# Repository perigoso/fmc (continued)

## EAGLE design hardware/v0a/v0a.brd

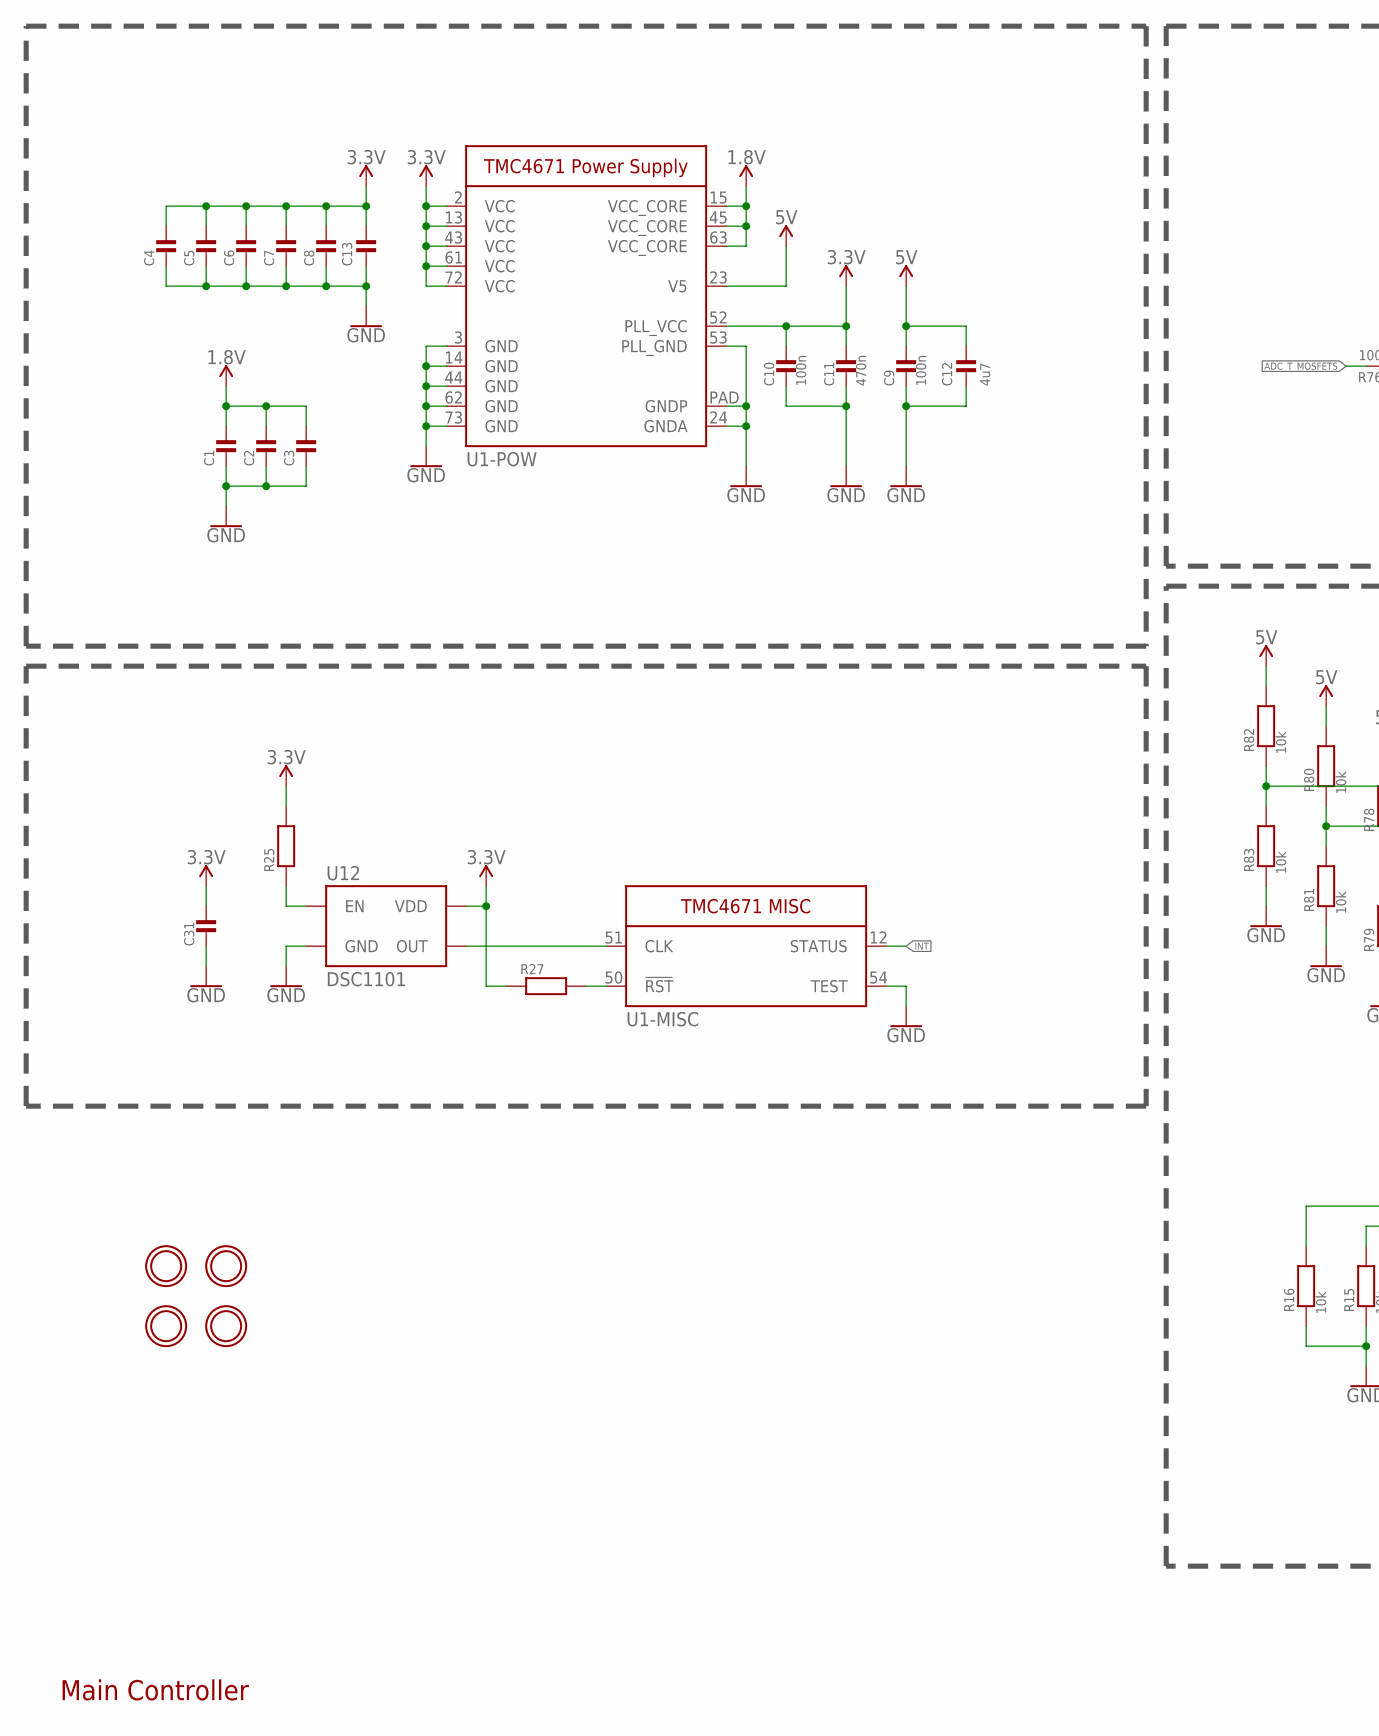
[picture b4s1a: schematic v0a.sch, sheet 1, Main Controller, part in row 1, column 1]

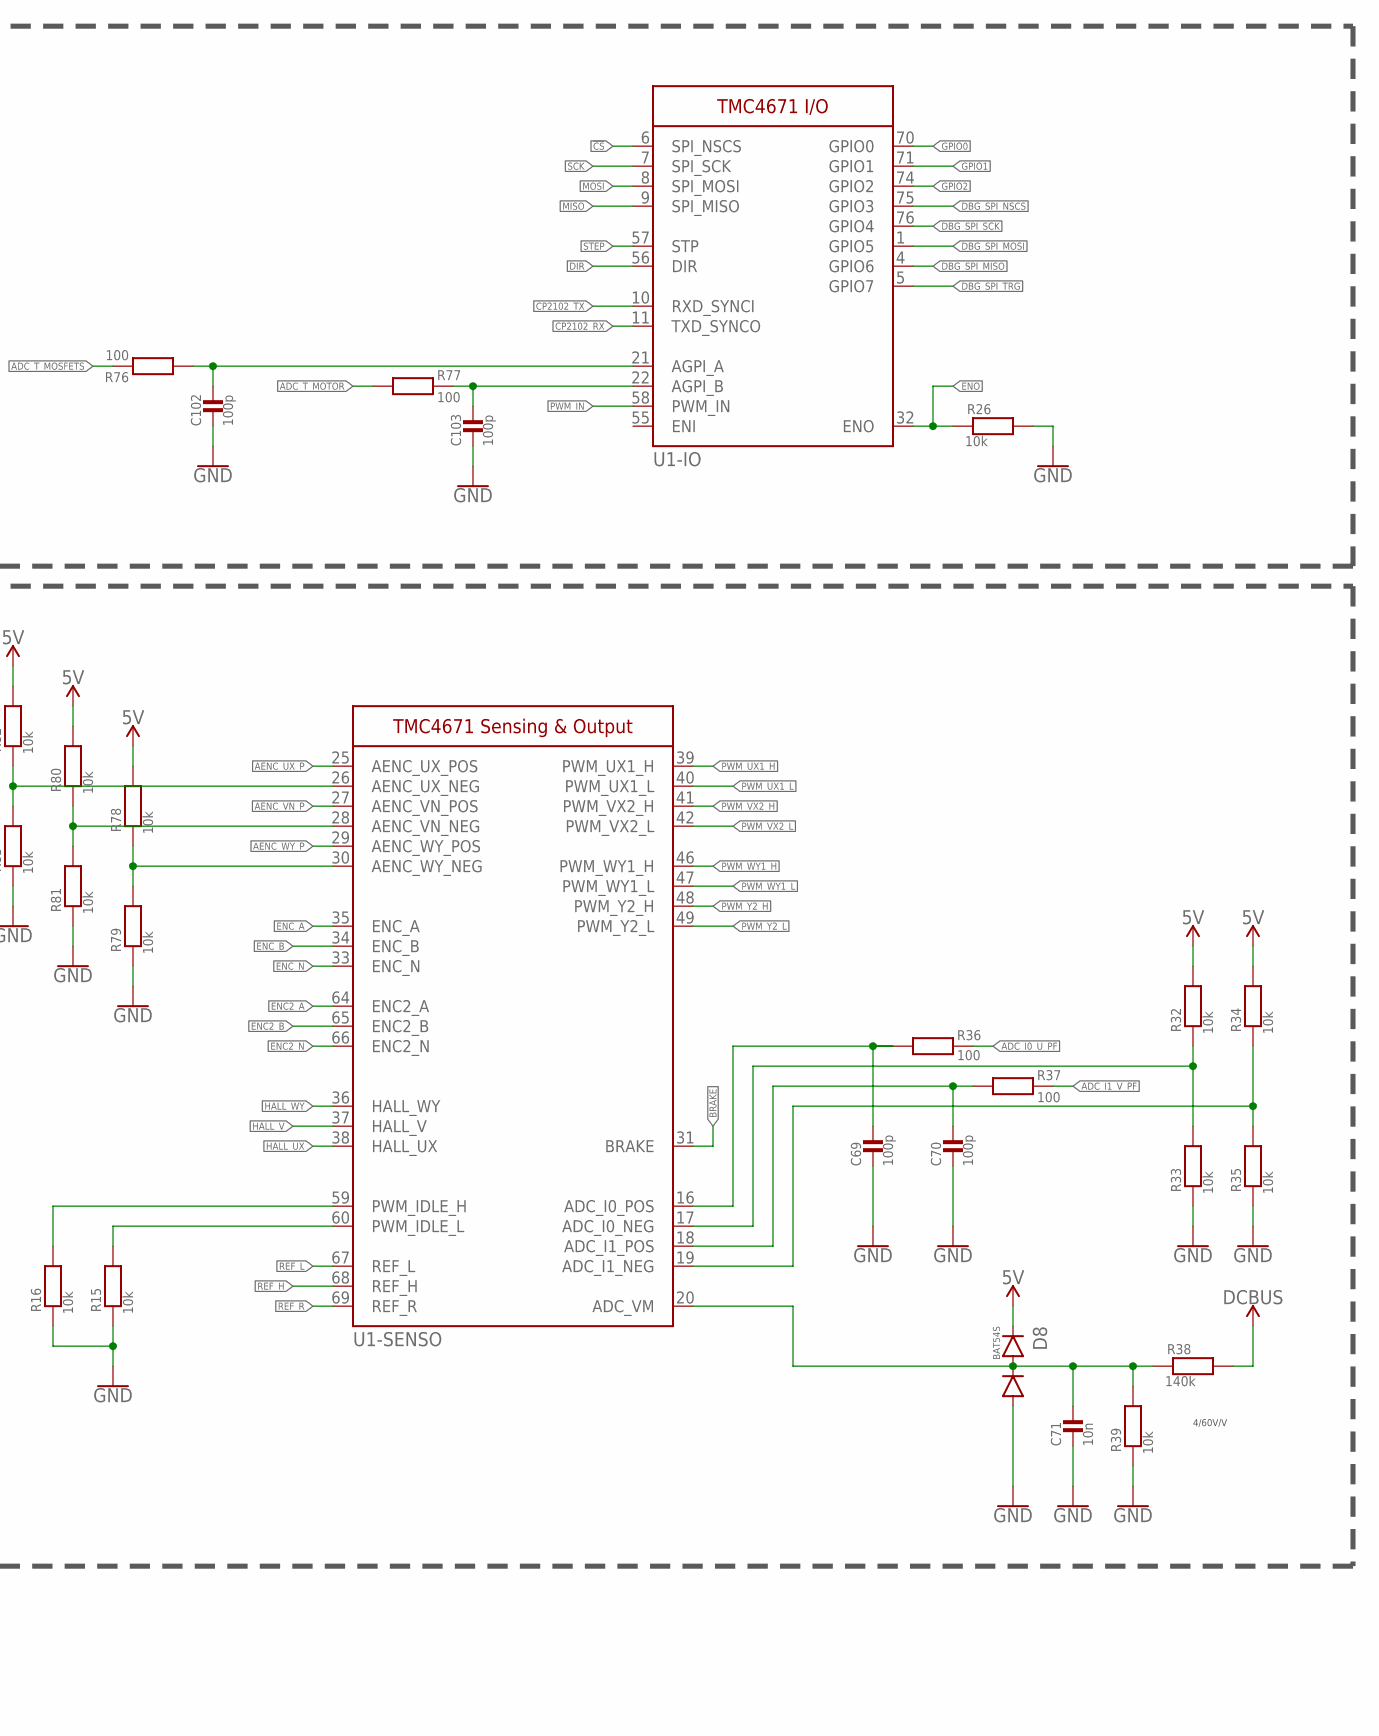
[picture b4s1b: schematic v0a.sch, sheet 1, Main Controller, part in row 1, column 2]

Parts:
C1, C2, C3, C4, C5, C6, C7, C8, C13, C31: MLCC0603; 0603_WAVE
C9, C10: 100n; 0603_WAVE
C11: 470n; 0603_WAVE
C12: 4u7; 0603_WAVE
C69, C70, C102, C103: 100p; 0603_WAVE
C71: 10n; 0603_WAVE
D8: BAT54S; SOT-23-3
R15, R16, R26, R32, R33, R34, R35, R39, R78, R79, R80, R81, R82, R83: 10k; 0603_WAVE
R25, R27: RESISTOR0603; 0603_WAVE
R36, R37, R76, R77: 100; 0603_WAVE
R38: 140k; 0603_WAVE
U1: TMC4671; QFN76
U12: DSC1101; CDFN_5X3.2
U$12, U$13, U$15, U$16: MOUNTINGHOLE3.0; MOUNTINGHOLE_3.0_PLATED

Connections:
1.8V: C1.P$1, C2.P$1, C3.P$1, U1.15 (VCC_CORE), U1.45 (VCC_CORE), U1.63 (VCC_CORE)
3.3V: C4.P$1, C5.P$1, C6.P$1, C7.P$1, C8.P$1, C10.P$1, C11.P$1, C13.P$1, C31.P$1, R25.P$2, R27.P$1, U1.2 (VCC), U1.13 (VCC), U1.43 (VCC), U1.52 (PLL_VCC), U1.61 (VCC), U1.72 (VCC), U12.6 (VDD); also elsewhere on the board
5V: C9.P$1, C12.P$1, D8.P$2 (2), R32.P$2, R34.P$2, R78.P$2, R80.P$2, R82.P$2, U1.23 (V5); also elsewhere on the board
!CS: U1.6 (SPI_NSCS); also elsewhere on the board
ADC_I0_U_PF: R36.P$2; also elsewhere on the board
ADC_I1_V_PF: R37.P$2; also elsewhere on the board
ADC_T_MOSFETS: R76.P$2; also elsewhere on the board
ADC_T_MOTOR: R77.P$1; also elsewhere on the board
AENC_UX_P: U1.25 (AENC_UX_POS); also elsewhere on the board
AENC_VN_P: U1.27 (AENC_VN_POS); also elsewhere on the board
AENC_WY_P: U1.29 (AENC_WY_POS); also elsewhere on the board
BRAKE: U1.31 (BRAKE); also elsewhere on the board
CP2102_RX: U1.11 (TXD_SYNCO); also elsewhere on the board
CP2102_TX: U1.10 (RXD_SYNCI); also elsewhere on the board
DBG_SPI_MISO: U1.4 (GPIO6); also elsewhere on the board
DBG_SPI_MOSI: U1.1 (GPIO5); also elsewhere on the board
DBG_SPI_NSCS: U1.75 (GPIO3); also elsewhere on the board
DBG_SPI_SCK: U1.76 (GPIO4); also elsewhere on the board
DBG_SPI_TRG: U1.5 (GPIO7); also elsewhere on the board
DCBUS: R38.P$2; also elsewhere on the board
DIR: U1.56 (DIR); also elsewhere on the board
ENC2_A: U1.64 (ENC2_A); also elsewhere on the board
ENC2_B: U1.65 (ENC2_B); also elsewhere on the board
ENC2_N: U1.66 (ENC2_N); also elsewhere on the board
ENC_A: U1.35 (ENC_A); also elsewhere on the board
ENC_B: U1.34 (ENC_B); also elsewhere on the board
ENC_N: U1.33 (ENC_N); also elsewhere on the board
ENO: R26.P$1, U1.32 (ENO); also elsewhere on the board
GND: C1.P$2, C2.P$2, C3.P$2, C4.P$2, C5.P$2, C6.P$2, C7.P$2, C8.P$2, C9.P$2, C10.P$2, C11.P$2, C12.P$2, C13.P$2, C31.P$2, C69.P$2, C70.P$2, C71.P$2, C102.P$2, C103.P$2, D8.P$1 (1), R15.P$1, R16.P$1, R26.P$2, R33.P$1, R35.P$1, R39.P$1, R79.P$1, R81.P$1, R83.P$1, U1.3 (GND), U1.14 (GND), U1.24 (GNDA), U1.44 (GND), U1.53 (PLL_GND), U1.54 (TEST), U1.62 (GND), U1.73 (GND), U1.PAD (GNDP), U12.3 (GND); also elsewhere on the board
GPIO0: U1.70 (GPIO0)
GPIO1: U1.71 (GPIO1)
GPIO2: U1.74 (GPIO2)
HALL_UX: U1.38 (HALL_UX); also elsewhere on the board
HALL_V: U1.37 (HALL_V); also elsewhere on the board
HALL_WY: U1.36 (HALL_WY); also elsewhere on the board
INT: U1.12 (STATUS); also elsewhere on the board
MISO: U1.9 (SPI_MISO); also elsewhere on the board
MOSI: U1.8 (SPI_MOSI); also elsewhere on the board
unnamed: R15.P$2, U1.60 (PWM_IDLE_L)
unnamed: R16.P$2, U1.59 (PWM_IDLE_H)
unnamed: U1.51 (CLK), U12.4 (OUT)
unnamed: R27.P$2, U1.50 (!RST!)
unnamed: R25.P$1, U12.1 (EN)
unnamed: C69.P$1, R36.P$1, U1.16 (ADC_I0_POS)
unnamed: C70.P$1, R37.P$1, U1.18 (ADC_I1_POS)
unnamed: R32.P$1, R33.P$2, U1.17 (ADC_I0_NEG)
unnamed: R34.P$1, R35.P$2, U1.19 (ADC_I1_NEG)
unnamed: C71.P$1, D8.P$3 (3), R38.P$1, R39.P$2, U1.20 (ADC_VM)
unnamed: C102.P$1, R76.P$1, U1.21 (AGPI_A)
unnamed: C103.P$1, R77.P$2, U1.22 (AGPI_B)
unnamed: R78.P$1, R79.P$2, U1.30 (AENC_WY_NEG)
unnamed: R80.P$1, R81.P$2, U1.28 (AENC_VN_NEG)
unnamed: R82.P$1, R83.P$2, U1.26 (AENC_UX_NEG)
PWM_IN: U1.58 (PWM_IN); also elsewhere on the board
PWM_UX1_H: U1.39 (PWM_UX1_H); also elsewhere on the board
PWM_UX1_L: U1.40 (PWM_UX1_L); also elsewhere on the board
PWM_VX2_H: U1.41 (PWM_VX2_H); also elsewhere on the board
PWM_VX2_L: U1.42 (PWM_VX2_L); also elsewhere on the board
PWM_WY1_H: U1.46 (PWM_WY1_H); also elsewhere on the board
PWM_WY1_L: U1.47 (PWM_WY1_L); also elsewhere on the board
PWM_Y2_H: U1.48 (PWM_Y2_H); also elsewhere on the board
PWM_Y2_L: U1.49 (PWM_Y2_L); also elsewhere on the board
REF_H: U1.68 (REF_H); also elsewhere on the board
REF_L: U1.67 (REF_L); also elsewhere on the board
REF_R: U1.69 (REF_R); also elsewhere on the board
SCK: U1.7 (SPI_SCK); also elsewhere on the board
STEP: U1.57 (STP); also elsewhere on the board

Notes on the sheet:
Main Controller
4/60V/V

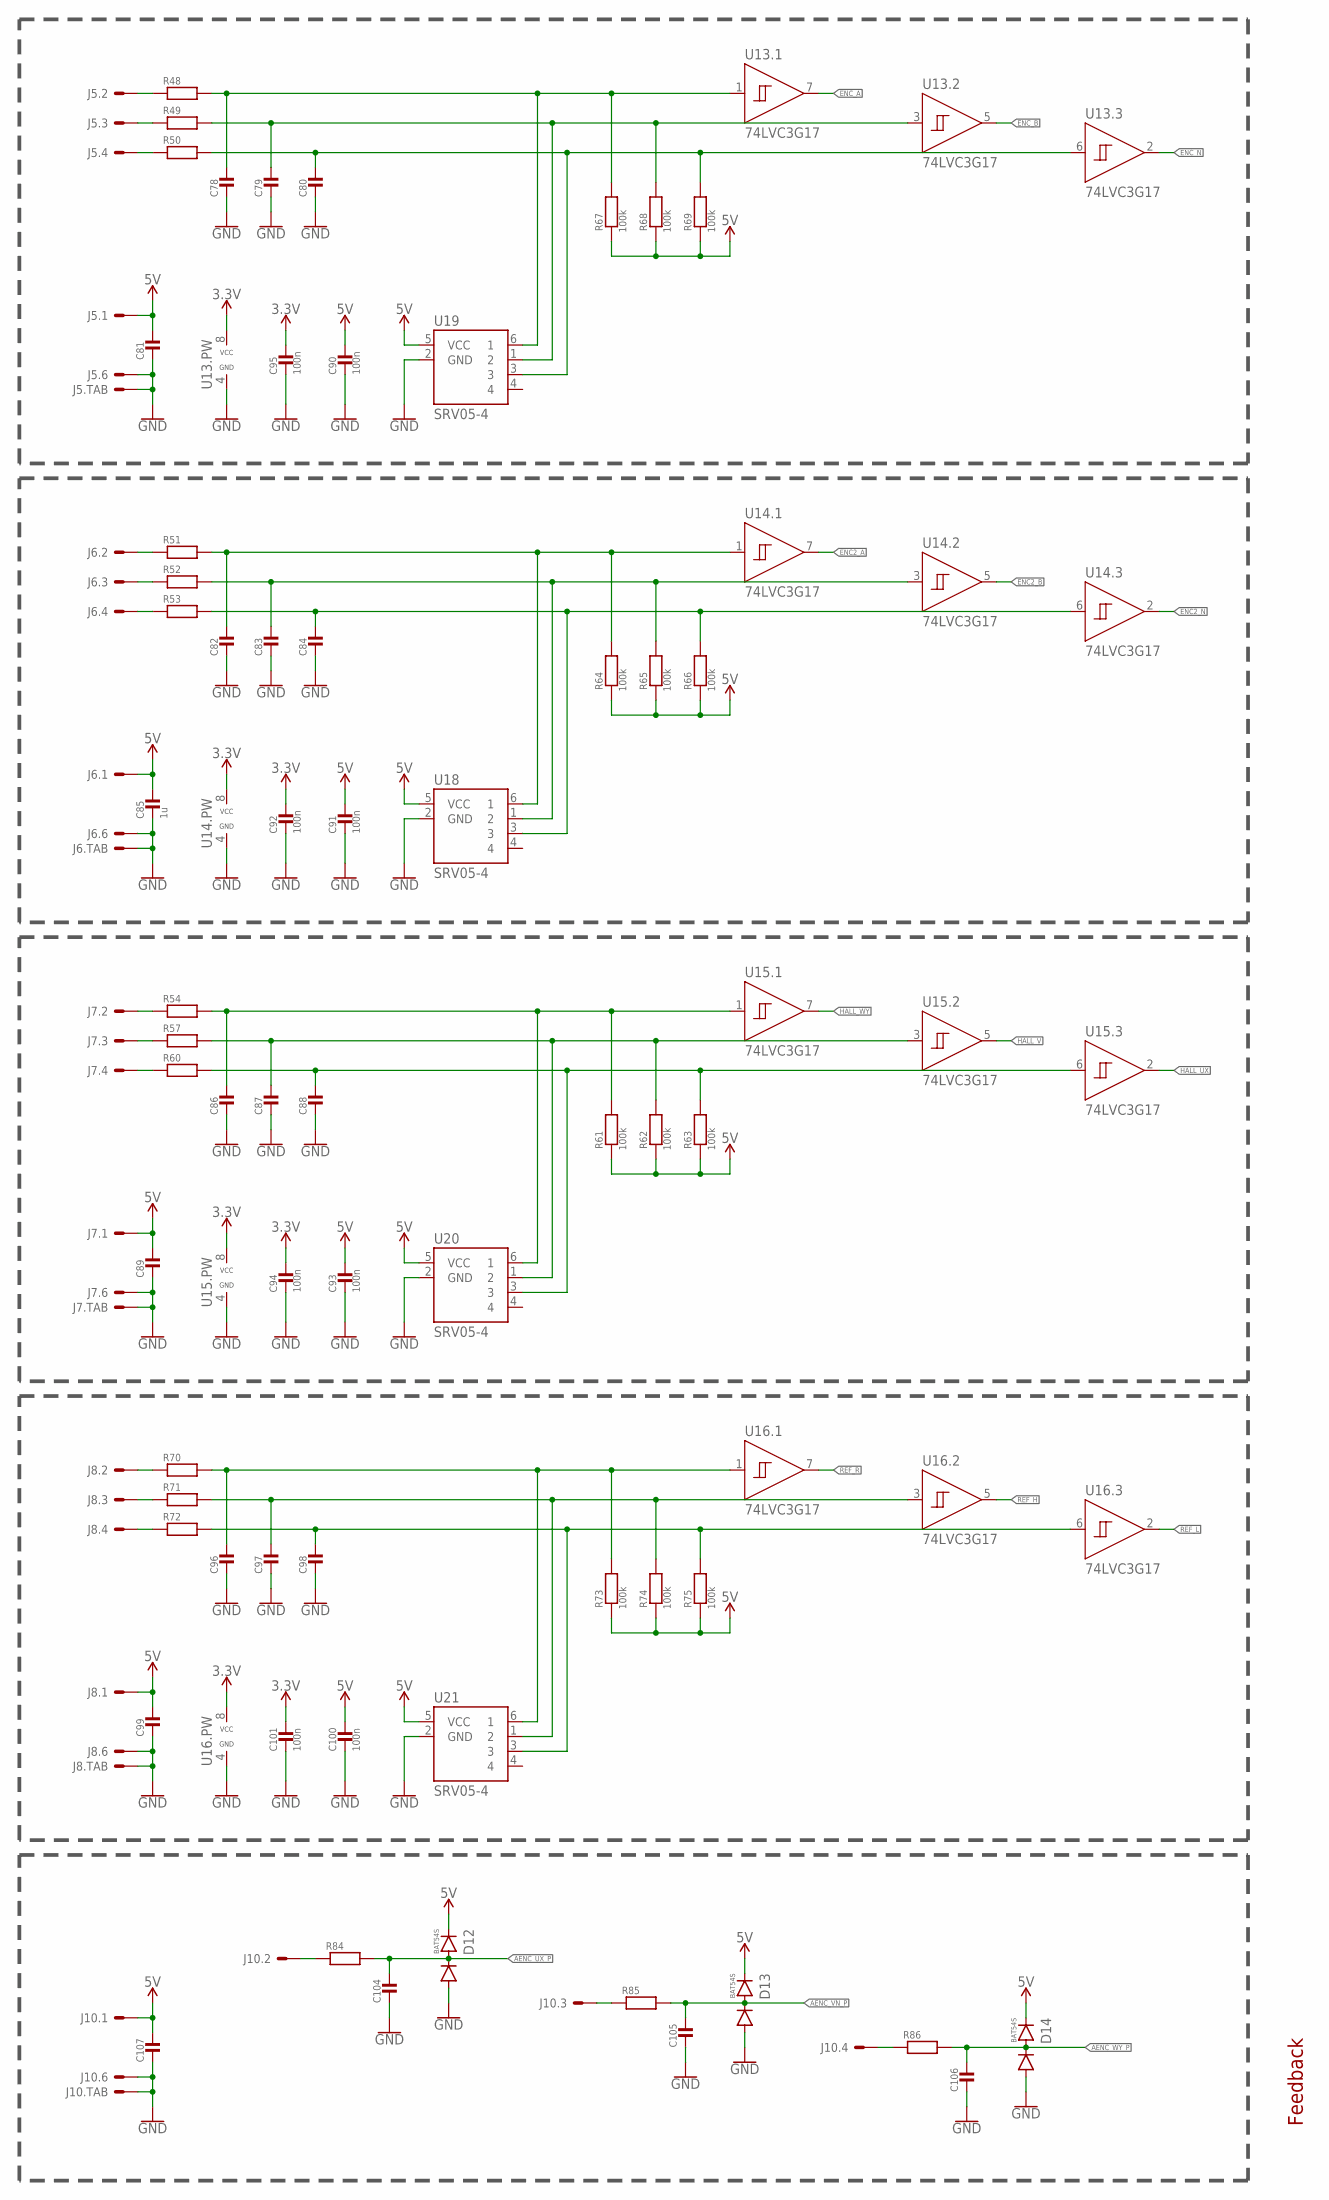
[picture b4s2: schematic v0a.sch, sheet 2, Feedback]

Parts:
C78, C79, C80, C81, C82, C83, C84, C86, C87, C88, C89, C96, C97, C98, C99, C104, C105, C106, C107: MLCC0603; 0603_WAVE
C85: 1u; 0603_WAVE
C90, C91, C92, C93, C94, C95, C100, C101: 100n; 0603_WAVE
D12, D13, D14: BAT54S; SOT-23-3
J5, J6, J7, J8, J10: SH-5; SM05B-SSR-H-TB
R48, R49, R50, R51, R52, R53, R54, R57, R60, R70, R71, R72, R84, R85, R86: RESISTOR0603; 0603_WAVE
R61, R62, R63, R64, R65, R66, R67, R68, R69, R73, R74, R75: 100k; 0603_WAVE
U13, U14, U15, U16: 74LVC3G17; TSSOP-8
U18, U19, U20, U21: SRV05-4; SOT23-6

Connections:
3.3V: C92.P$1, C94.P$1, C95.P$1, C101.P$1, U13.8 (VCC), U14.8 (VCC), U15.8 (VCC), U16.8 (VCC); also elsewhere on the board
5V: C81.P$1, C85.P$1, C89.P$1, C90.P$1, C91.P$1, C93.P$1, C99.P$1, C100.P$1, C107.P$1, D12.P$2 (2), D13.P$2 (2), D14.P$2 (2), J5.1, J6.1, J7.1, J8.1, J10.1, R61.P$1, R62.P$1, R63.P$1, R64.P$1, R65.P$1, R66.P$1, R67.P$1, R68.P$1, R69.P$1, R73.P$1, R74.P$1, R75.P$1, U18.5 (VCC), U19.5 (VCC), U20.5 (VCC), U21.5 (VCC); also elsewhere on the board
AENC_UX_P: C104.P$1, D12.P$3 (3), R84.P$2; also elsewhere on the board
AENC_VN_P: C105.P$1, D13.P$3 (3), R85.P$2; also elsewhere on the board
AENC_WY_P: C106.P$1, D14.P$3 (3), R86.P$2; also elsewhere on the board
ENC2_A: U14.7 (Y); also elsewhere on the board
ENC2_B: U14.5 (Y); also elsewhere on the board
ENC2_N: U14.2 (Y); also elsewhere on the board
ENC_A: U13.7 (Y); also elsewhere on the board
ENC_B: U13.5 (Y); also elsewhere on the board
ENC_N: U13.2 (Y); also elsewhere on the board
GND: C78.P$2, C79.P$2, C80.P$2, C81.P$2, C82.P$2, C83.P$2, C84.P$2, C85.P$2, C86.P$2, C87.P$2, C88.P$2, C89.P$2, C90.P$2, C91.P$2, C92.P$2, C93.P$2, C94.P$2, C95.P$2, C96.P$2, C97.P$2, C98.P$2, C99.P$2, C100.P$2, C101.P$2, C104.P$2, C105.P$2, C106.P$2, C107.P$2, D12.P$1 (1), D13.P$1 (1), D14.P$1 (1), J5.5, J5.FIT@1, J5.FIT@2, J6.5, J6.FIT@1, J6.FIT@2, J7.5, J7.FIT@1, J7.FIT@2, J8.5, J8.FIT@1, J8.FIT@2, J10.5, J10.FIT@1, J10.FIT@2, U13.4 (GND), U14.4 (GND), U15.4 (GND), U16.4 (GND), U18.2 (GND), U19.2 (GND), U20.2 (GND), U21.2 (GND); also elsewhere on the board
HALL_UX: U15.2 (Y); also elsewhere on the board
HALL_V: U15.5 (Y); also elsewhere on the board
HALL_WY: U15.7 (Y); also elsewhere on the board
unnamed: C80.P$1, R50.P$2, R69.P$2, U13.6 (A), U19.3
unnamed: C79.P$1, R49.P$2, R68.P$2, U13.3 (A), U19.1 (2)
unnamed: C84.P$1, R53.P$2, R66.P$2, U14.6 (A), U18.3
unnamed: J5.2, R48.P$1
unnamed: J5.3, R49.P$1
unnamed: J5.4, R50.P$1
unnamed: C78.P$1, R48.P$2, R67.P$2, U13.1 (A), U19.6 (1)
unnamed: C83.P$1, R52.P$2, R65.P$2, U14.3 (A), U18.1 (2)
unnamed: J6.2, R51.P$1
unnamed: J6.3, R52.P$1
unnamed: J6.4, R53.P$1
unnamed: C82.P$1, R51.P$2, R64.P$2, U14.1 (A), U18.6 (1)
unnamed: C88.P$1, R60.P$2, R63.P$2, U15.6 (A), U20.3
unnamed: C87.P$1, R57.P$2, R62.P$2, U15.3 (A), U20.1 (2)
unnamed: J7.2, R54.P$1
unnamed: J7.3, R57.P$1
unnamed: J7.4, R60.P$1
unnamed: C86.P$1, R54.P$2, R61.P$2, U15.1 (A), U20.6 (1)
unnamed: C98.P$1, R72.P$2, R75.P$2, U16.6 (A), U21.3
unnamed: C97.P$1, R71.P$2, R74.P$2, U16.3 (A), U21.1 (2)
unnamed: J8.2, R70.P$1
unnamed: J8.3, R71.P$1
unnamed: J8.4, R72.P$1
unnamed: C96.P$1, R70.P$2, R73.P$2, U16.1 (A), U21.6 (1)
unnamed: J10.4, R86.P$1
unnamed: J10.3, R85.P$1
unnamed: J10.2, R84.P$1
REF_H: U16.5 (Y); also elsewhere on the board
REF_L: U16.2 (Y); also elsewhere on the board
REF_R: U16.7 (Y); also elsewhere on the board

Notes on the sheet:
Feedback

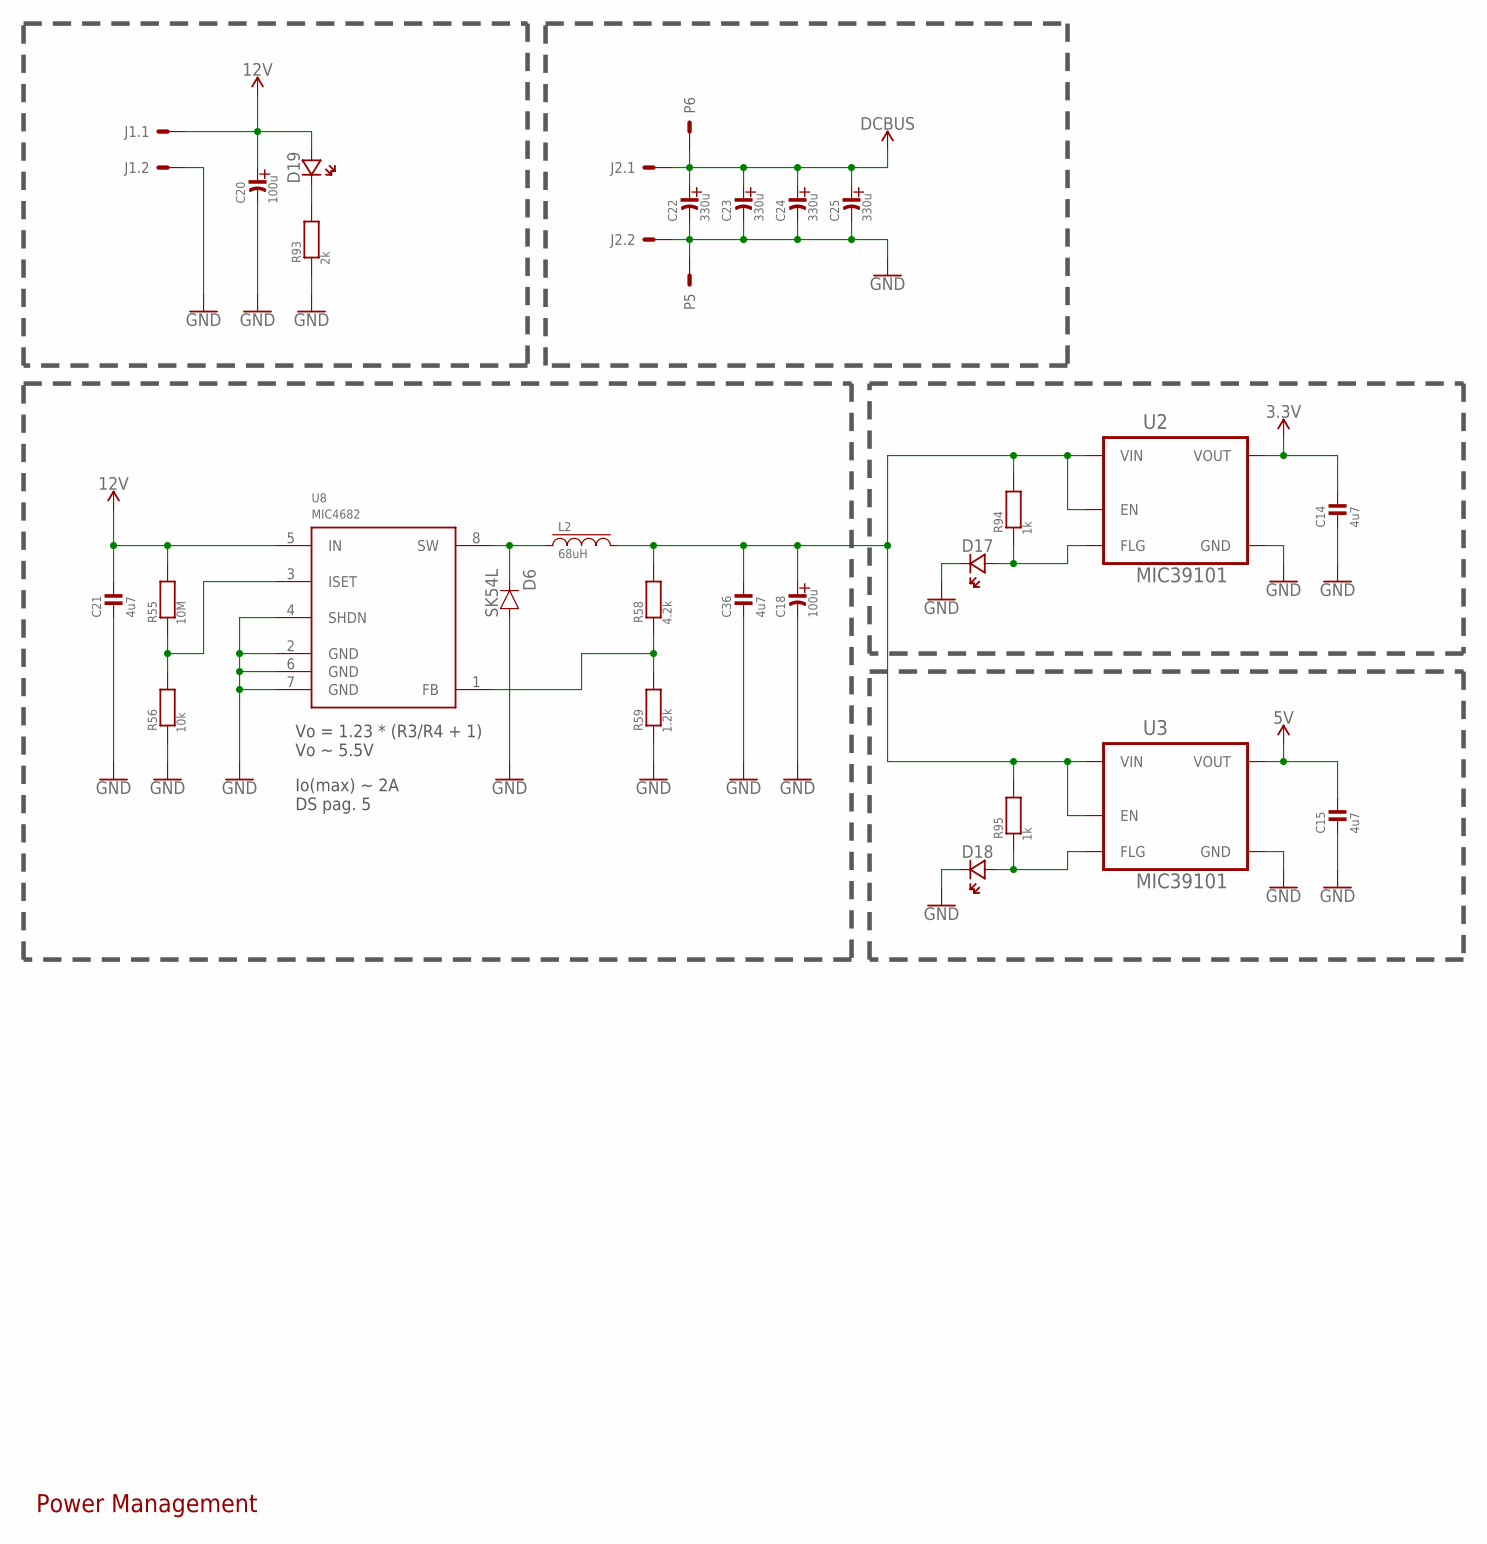
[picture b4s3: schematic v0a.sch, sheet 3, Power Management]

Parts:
C14, C15, C21, C36: 4u7; 0603_WAVE
C18, C20: 100u; PANASONIC_D
C22, C23, C24, C25: 330u; PANASONIC_G
D6: SK54L; DO214AA
D17, D18, D19: LED0603; CHIPLED_0603
J1, J2: 2P-6.35P
L2: 68uH; CDRH104R
P5, P6: POWPAD; TH-HP
R55: 10M; 0603_WAVE
R56: 10k; 0603_WAVE
R58: 4.2k; 0603_WAVE
R59: 1.2k; 0603_WAVE
R93: 2k; 0603_WAVE
R94, R95: 1k; 0603_WAVE
U2, U3: MIC39101; SOIC8
U8: MIC4682; SOIC8

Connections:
3.3V: C14.P$1, U2.3 (VOUT); also elsewhere on the board
5V: C15.P$1, U3.3 (VOUT); also elsewhere on the board
12V: C20.+ (AN), C21.P$1, D19.A (AN), J1.1, R55.P$2, U8.5 (IN); also elsewhere on the board
DCBUS: C22.+ (AN), C23.+ (AN), C24.+ (AN), C25.+ (AN), J2.1, P6.H1, P6.H2, P6.H3, P6.H4, P6.H5, P6.H6, P6.H7, P6.H8, P6.H9, P6.H10, P6.H11, P6.H12, P6.PAD; also elsewhere on the board
GND: C14.P$2, C15.P$2, C18.- (CA), C20.- (CA), C21.P$2, C22.- (CA), C23.- (CA), C24.- (CA), C25.- (CA), C36.P$2, D6.A, D17.C (CA), D18.C (CA), J1.2, J2.2, P5.H1, P5.H2, P5.H3, P5.H4, P5.H5, P5.H6, P5.H7, P5.H8, P5.H9, P5.H10, P5.H11, P5.H12, P5.PAD, R56.P$1, R59.P$1, R93.P$1, U2.5 (GND), U2.6 (GND), U2.7 (GND), U2.8 (GND), U3.5 (GND), U3.6 (GND), U3.7 (GND), U3.8 (GND), U8.2 (GND), U8.4 (SHDN), U8.6 (GND), U8.7 (GND); also elsewhere on the board
unnamed: C18.+ (AN), C36.P$1, L2.2, R58.P$2, R94.P$2, R95.P$2, U2.1 (EN), U2.2 (VIN), U3.1 (EN), U3.2 (VIN)
unnamed: D6.C, L2.1, U8.8 (SW)
unnamed: R58.P$1, R59.P$2, U8.1 (FB)
unnamed: R55.P$1, R56.P$2, U8.3 (ISET)
unnamed: D17.A (AN), R94.P$1, U2.4 (FLG)
unnamed: D19.C (CA), R93.P$2
unnamed: D18.A (AN), R95.P$1, U3.4 (FLG)

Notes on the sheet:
Power Management
Vo = 1.23 * (R3/R4 + 1) Vo ~ 5.5V
Io(max) ~ 2A DS pag. 5

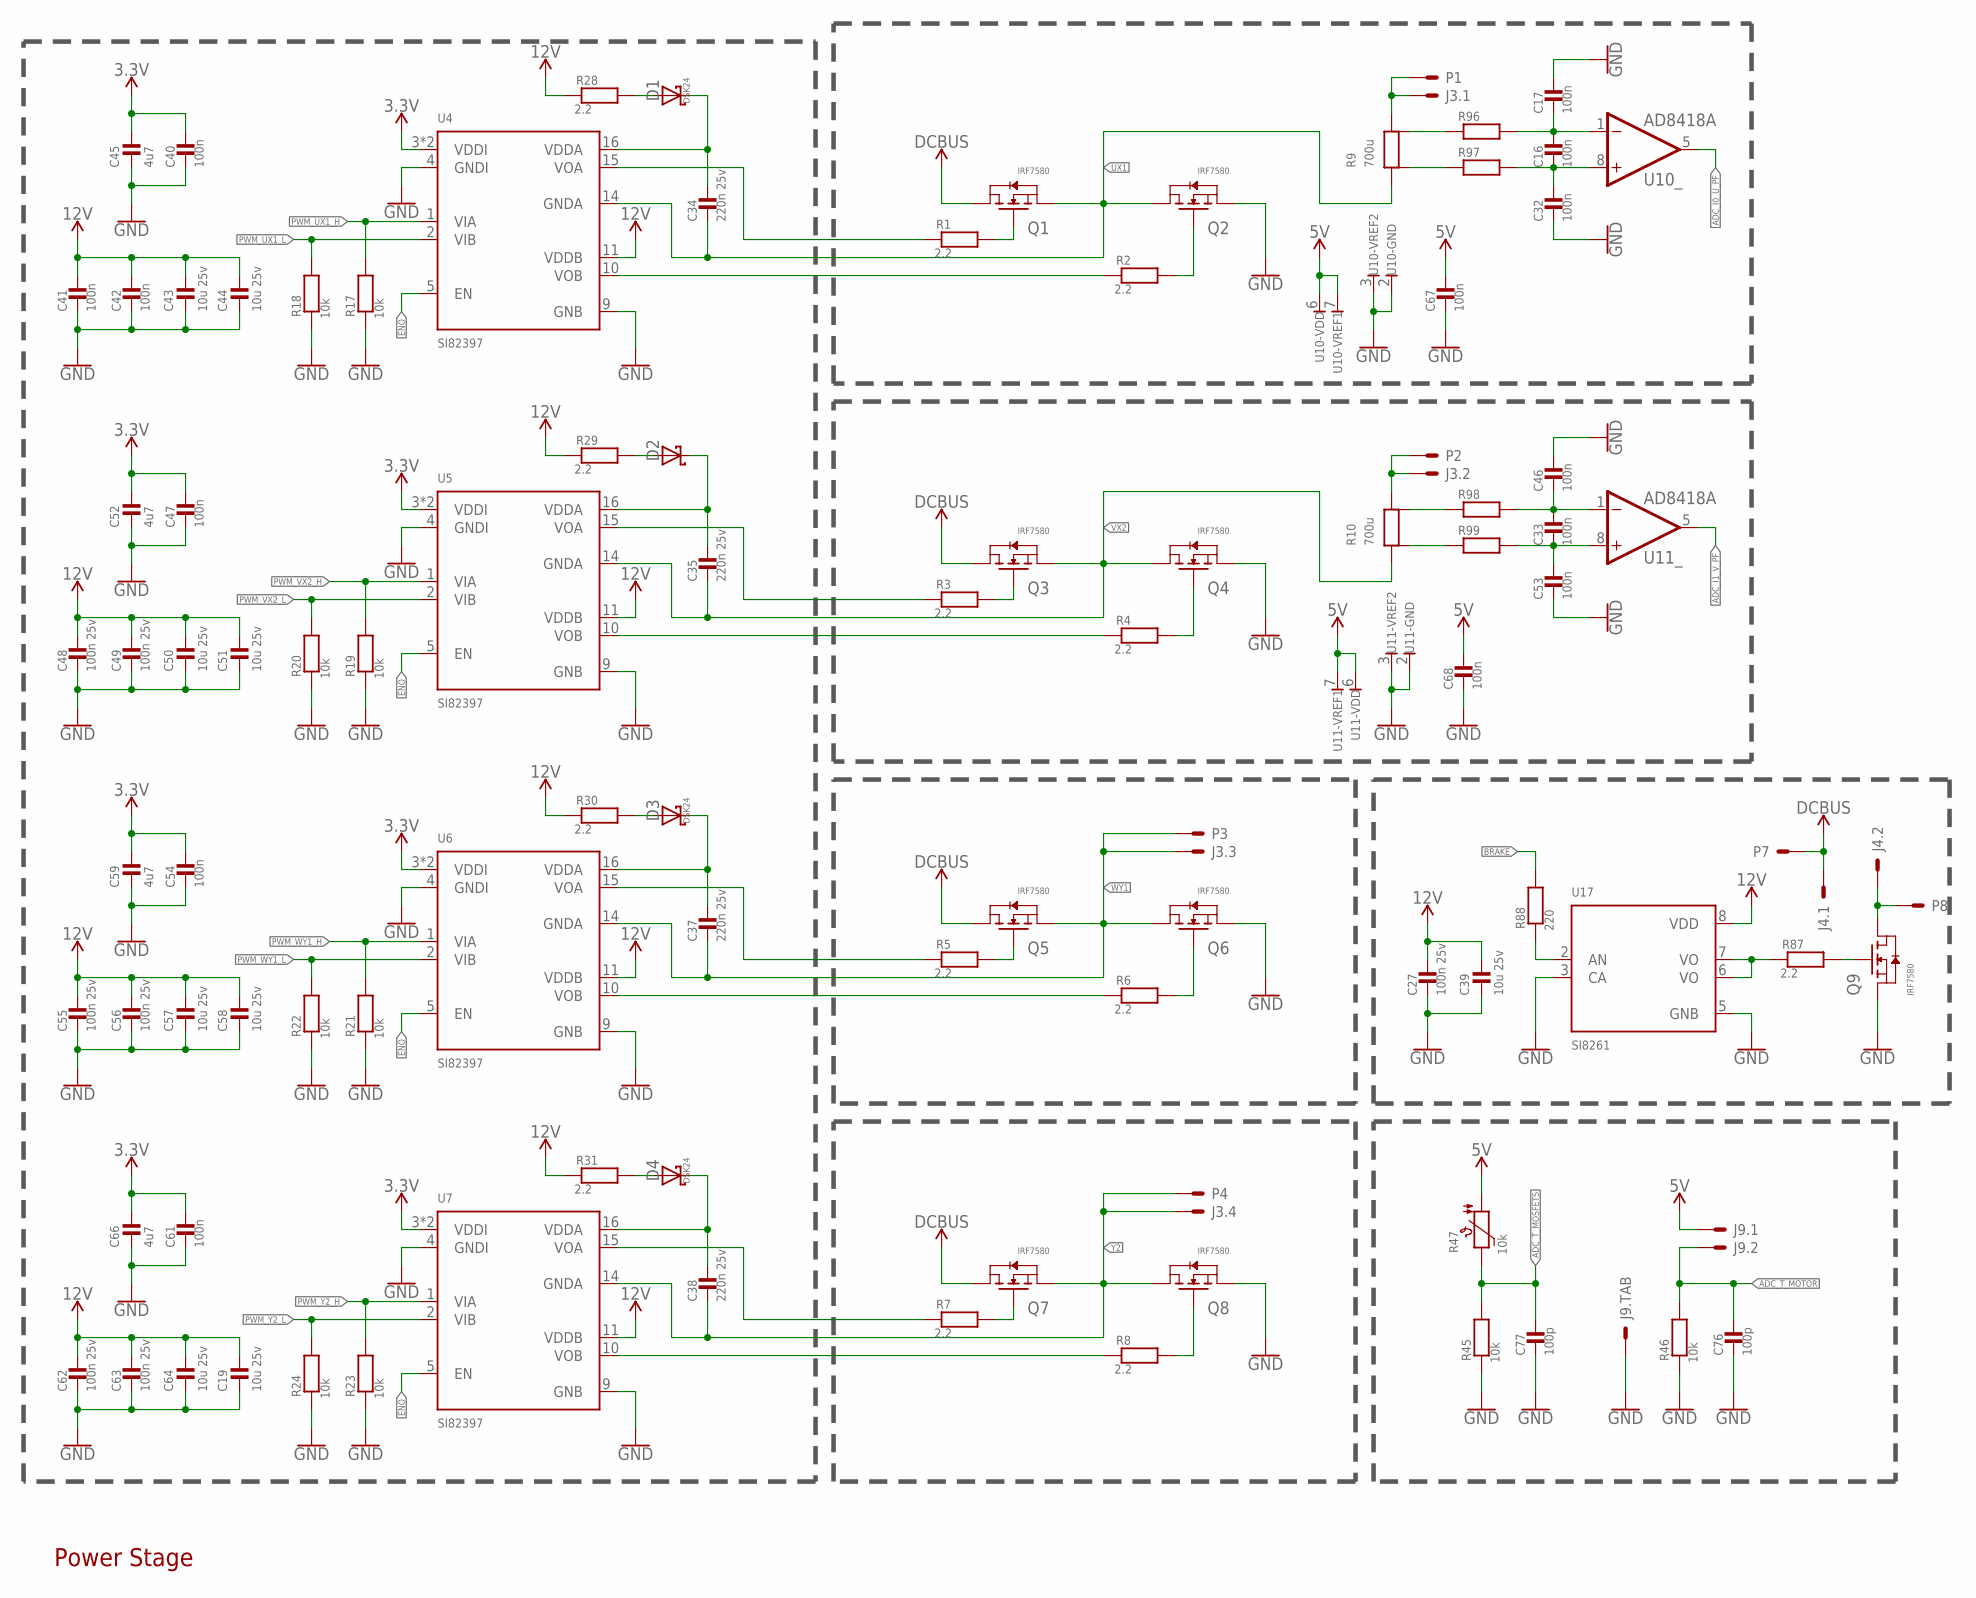
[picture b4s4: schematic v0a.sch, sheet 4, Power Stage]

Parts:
C16, C17, C32, C33, C40, C41, C42, C46, C47, C53, C54, C61, C67, C68: 100n; 0603_WAVE
C19, C39, C43, C44, C50, C51, C57, C58, C64: 10u 25v; 0603_WAVE
C27, C48, C49, C55, C56, C62, C63: 100n 25v; 0603_WAVE
C34, C35, C37, C38: 220n 25v; 0603_WAVE
C45, C52, C59, C66: 4u7; 0603_WAVE
C76, C77: 100p; 0603_WAVE
D1, D2, D3, D4: DSK24; SOD-123
J3: 4P-6.35P
J4: 2P-6.35P
J9: SH-2; SM02B-SSR-H-TB
P1, P2, P3, P4, P7, P8: POWPAD; TH-HP
Q1, Q2, Q3, Q4, Q5, Q6, Q7, Q8, Q9: IRF7580; DIRECTFET-ME
R1, R2, R3, R4, R5, R6, R7, R8, R28, R29, R30, R31, R87: 2.2; 0603_WAVE
R9, R10: 700u; 3920
R17, R18, R19, R20, R21, R22, R23, R24, R45, R46, R47: 10k; 0603_WAVE
R88: 220; 0603_WAVE
R96, R97, R98, R99: RESISTOR0603; 0603_WAVE
U4, U5, U6, U7: SI82397; SOIC-16-WB
U10, U11: AD8418A; MSOP-8
U17: SI8261; SOIC_8

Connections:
3.3V: C40.P$1, C45.P$1, C47.P$1, C52.P$1, C54.P$1, C59.P$1, C61.P$1, C66.P$1, U4.3 (VDDI), U4.8 (VDDI), U5.3 (VDDI), U5.8 (VDDI), U6.3 (VDDI), U6.8 (VDDI), U7.3 (VDDI), U7.8 (VDDI); also elsewhere on the board
5V: C67.P$1, C68.P$1, J9.1, R47.P$2, U10.6, U10.7, U11.6, U11.7; also elsewhere on the board
12V: C19.P$1, C27.P$1, C39.P$1, C41.P$1, C42.P$1, C43.P$1, C44.P$1, C48.P$1, C49.P$1, C50.P$1, C51.P$1, C55.P$1, C56.P$1, C57.P$1, C58.P$1, C62.P$1, C63.P$1, C64.P$1, R28.P$1, R29.P$1, R30.P$1, R31.P$1, U4.11 (VDDB), U5.11 (VDDB), U6.11 (VDDB), U7.11 (VDDB), U17.8 (VDD); also elsewhere on the board
ADC_I0_U_PF: U10.5 (O); also elsewhere on the board
ADC_I1_V_PF: U11.5 (O); also elsewhere on the board
ADC_T_MOSFETS: C77.P$1, R45.P$2, R47.P$1; also elsewhere on the board
ADC_T_MOTOR: C76.P$1, J9.2, R46.P$2; also elsewhere on the board
BRAKE: R88.P$2; also elsewhere on the board
DCBUS: J4.1, P7.H1, P7.H2, P7.H3, P7.H4, P7.H5, P7.H6, P7.H7, P7.H8, P7.H9, P7.H10, P7.H11, P7.H12, P7.PAD, Q1.D1, Q1.D2 (D1), Q1.D3 (D1), Q1.D4 (D1), Q3.D1, Q3.D2 (D1), Q3.D3 (D1), Q3.D4 (D1), Q5.D1, Q5.D2 (D1), Q5.D3 (D1), Q5.D4 (D1), Q7.D1, Q7.D2 (D1), Q7.D3 (D1), Q7.D4 (D1); also elsewhere on the board
ENO: U4.5 (EN), U5.5 (EN), U6.5 (EN), U7.5 (EN); also elsewhere on the board
GND: C17.P$1, C19.P$2, C27.P$2, C32.P$2, C39.P$2, C40.P$2, C41.P$2, C42.P$2, C43.P$2, C44.P$2, C45.P$2, C46.P$1, C47.P$2, C48.P$2, C49.P$2, C50.P$2, C51.P$2, C52.P$2, C53.P$2, C54.P$2, C55.P$2, C56.P$2, C57.P$2, C58.P$2, C59.P$2, C61.P$2, C62.P$2, C63.P$2, C64.P$2, C66.P$2, C67.P$2, C68.P$2, C76.P$2, C77.P$2, J9.FIT@1, J9.FIT@2, Q2.S1, Q2.S2 (S1), Q2.S3 (S1), Q2.S4 (S1), Q2.S5 (S1), Q4.S1, Q4.S2 (S1), Q4.S3 (S1), Q4.S4 (S1), Q4.S5 (S1), Q6.S1, Q6.S2 (S1), Q6.S3 (S1), Q6.S4 (S1), Q6.S5 (S1), Q8.S1, Q8.S2 (S1), Q8.S3 (S1), Q8.S4 (S1), Q8.S5 (S1), Q9.S1, Q9.S2 (S1), Q9.S3 (S1), Q9.S4 (S1), Q9.S5 (S1), R17.P$1, R18.P$1, R19.P$1, R20.P$1, R21.P$1, R22.P$1, R23.P$1, R24.P$1, R45.P$1, R46.P$1, U4.4 (GNDI), U4.9 (GNB), U5.4 (GNDI), U5.9 (GNB), U6.4 (GNDI), U6.9 (GNB), U7.4 (GNDI), U7.9 (GNB), U10.2, U10.3, U11.2, U11.3, U17.3 (CA), U17.5 (GNB); also elsewhere on the board
unnamed: R1.P$1, U4.15 (VOA)
unnamed: Q2.G (G1), R2.P$2
unnamed: R9.SENSE+, R97.P$1
unnamed: C34.P$1, D1.C, U4.16 (VDDA)
unnamed: R3.P$1, U5.15 (VOA)
unnamed: Q4.G (G1), R4.P$2
unnamed: R9.SENSE-, R96.P$1
unnamed: C35.P$1, D2.C, U5.16 (VDDA)
unnamed: R5.P$1, U6.15 (VOA)
unnamed: Q6.G (G1), R6.P$2
unnamed: C16.P$1, C17.P$2, R96.P$2, U10.1 (IN-)
unnamed: C37.P$1, D3.C, U6.16 (VDDA)
unnamed: R7.P$1, U7.15 (VOA)
unnamed: Q8.G (G1), R8.P$2
unnamed: C16.P$2, C32.P$1, R97.P$2, U10.8 (IN+)
unnamed: C38.P$1, D4.C, U7.16 (VDDA)
unnamed: Q5.G (G1), R5.P$2
unnamed: Q1.G (G1), R1.P$2
unnamed: Q3.G (G1), R3.P$2
unnamed: Q7.G (G1), R7.P$2
unnamed: R2.P$1, U4.10 (VOB)
unnamed: R4.P$1, U5.10 (VOB)
unnamed: R6.P$1, U6.10 (VOB)
unnamed: R8.P$1, U7.10 (VOB)
unnamed: J3.2, P2.H1, P2.H2, P2.H3, P2.H4, P2.H5, P2.H6, P2.H7, P2.H8, P2.H9, P2.H10, P2.H11, P2.H12, P2.PAD, R10.3, R10.4
unnamed: J3.1, P1.H1, P1.H2, P1.H3, P1.H4, P1.H5, P1.H6, P1.H7, P1.H8, P1.H9, P1.H10, P1.H11, P1.H12, P1.PAD, R9.3, R9.4
unnamed: D4.A, R31.P$2
unnamed: D3.A, R30.P$2
unnamed: D2.A, R29.P$2
unnamed: D1.A, R28.P$2
unnamed: R10.SENSE-, R98.P$1
unnamed: R10.SENSE+, R99.P$1
unnamed: C33.P$2, C53.P$1, R99.P$2, U11.8 (IN+)
unnamed: C33.P$1, C46.P$2, R98.P$2, U11.1 (IN-)
unnamed: R88.P$1, U17.2 (AN)
unnamed: Q9.G (G1), R87.P$2
unnamed: R87.P$1, U17.6 (VO), U17.7 (VO)
unnamed: J4.2, P8.H1, P8.H2, P8.H3, P8.H4, P8.H5, P8.H6, P8.H7, P8.H8, P8.H9, P8.H10, P8.H11, P8.H12, P8.PAD, Q9.D1, Q9.D2 (D1), Q9.D3 (D1), Q9.D4 (D1)
PWM_UX1_H: R17.P$2, U4.1 (VIA); also elsewhere on the board
PWM_UX1_L: R18.P$2, U4.2 (VIB); also elsewhere on the board
PWM_VX2_H: R19.P$2, U5.1 (VIA); also elsewhere on the board
PWM_VX2_L: R20.P$2, U5.2 (VIB); also elsewhere on the board
PWM_WY1_H: R21.P$2, U6.1 (VIA); also elsewhere on the board
PWM_WY1_L: R22.P$2, U6.2 (VIB); also elsewhere on the board
PWM_Y2_H: R23.P$2, U7.1 (VIA); also elsewhere on the board
PWM_Y2_L: R24.P$2, U7.2 (VIB); also elsewhere on the board
UX1: C34.P$2, Q1.S1, Q1.S2 (S1), Q1.S3 (S1), Q1.S4 (S1), Q1.S5 (S1), Q2.D1, Q2.D2 (D1), Q2.D3 (D1), Q2.D4 (D1), R9.1, R9.2, U4.14 (GNDA)
VX2: C35.P$2, Q3.S1, Q3.S2 (S1), Q3.S3 (S1), Q3.S4 (S1), Q3.S5 (S1), Q4.D1, Q4.D2 (D1), Q4.D3 (D1), Q4.D4 (D1), R10.1, R10.2, U5.14 (GNDA)
WY1: C37.P$2, J3.3, P3.H1, P3.H2, P3.H3, P3.H4, P3.H5, P3.H6, P3.H7, P3.H8, P3.H9, P3.H10, P3.H11, P3.H12, P3.PAD, Q5.S1, Q5.S2 (S1), Q5.S3 (S1), Q5.S4 (S1), Q5.S5 (S1), Q6.D1, Q6.D2 (D1), Q6.D3 (D1), Q6.D4 (D1), U6.14 (GNDA)
Y2: C38.P$2, J3.4, P4.H1, P4.H2, P4.H3, P4.H4, P4.H5, P4.H6, P4.H7, P4.H8, P4.H9, P4.H10, P4.H11, P4.H12, P4.PAD, Q7.S1, Q7.S2 (S1), Q7.S3 (S1), Q7.S4 (S1), Q7.S5 (S1), Q8.D1, Q8.D2 (D1), Q8.D3 (D1), Q8.D4 (D1), U7.14 (GNDA)

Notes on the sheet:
Power Stage
